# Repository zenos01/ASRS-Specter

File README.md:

# Fiber Optic FPV System

A **DIY Fiber Optic-enabled FPV video and control system** designed for affordable, high-performance drone operation. This system uses off-the-shelf components to deliver interference-free communication and advanced features at a cost of around **$300**.

## Key Features
- **Fiber Optic Communication**: Reliable and interference-free in challenging environments.
- **Customizable and Open Source**: Fully programmable, allowing for custom OSD elements, unique arming methods, and feature expansion.
- **High-Performance Video**:
  - Supports **1600x900 at 60fps** and **720p at 120fps**.
- **Advanced Capabilities**:
  - Real-time trajectory estimation for precise object dropping or landings.
  - Multi-camera support for enhanced situational awareness.
  - Ground station processing for greater computational power and flexibility.

## About the Project
This project aims to provide an affordable, flexible, and customizable alternative to traditional FPV systems. While still a prototype, it’s open to collaboration and feedback to refine and expand its capabilities.

## Getting Started
The **hardware guide** and **software guide** are currently a work in progress, but the basic setup will be updated soon. Stay tuned for detailed instructions!

## Contributing
Contributions are welcome! You can:
- Report issues via [GitHub Issues](link-to-issues).
- Suggest features or improvements.
- Submit pull requests to help refine the project.

---

Thank you.

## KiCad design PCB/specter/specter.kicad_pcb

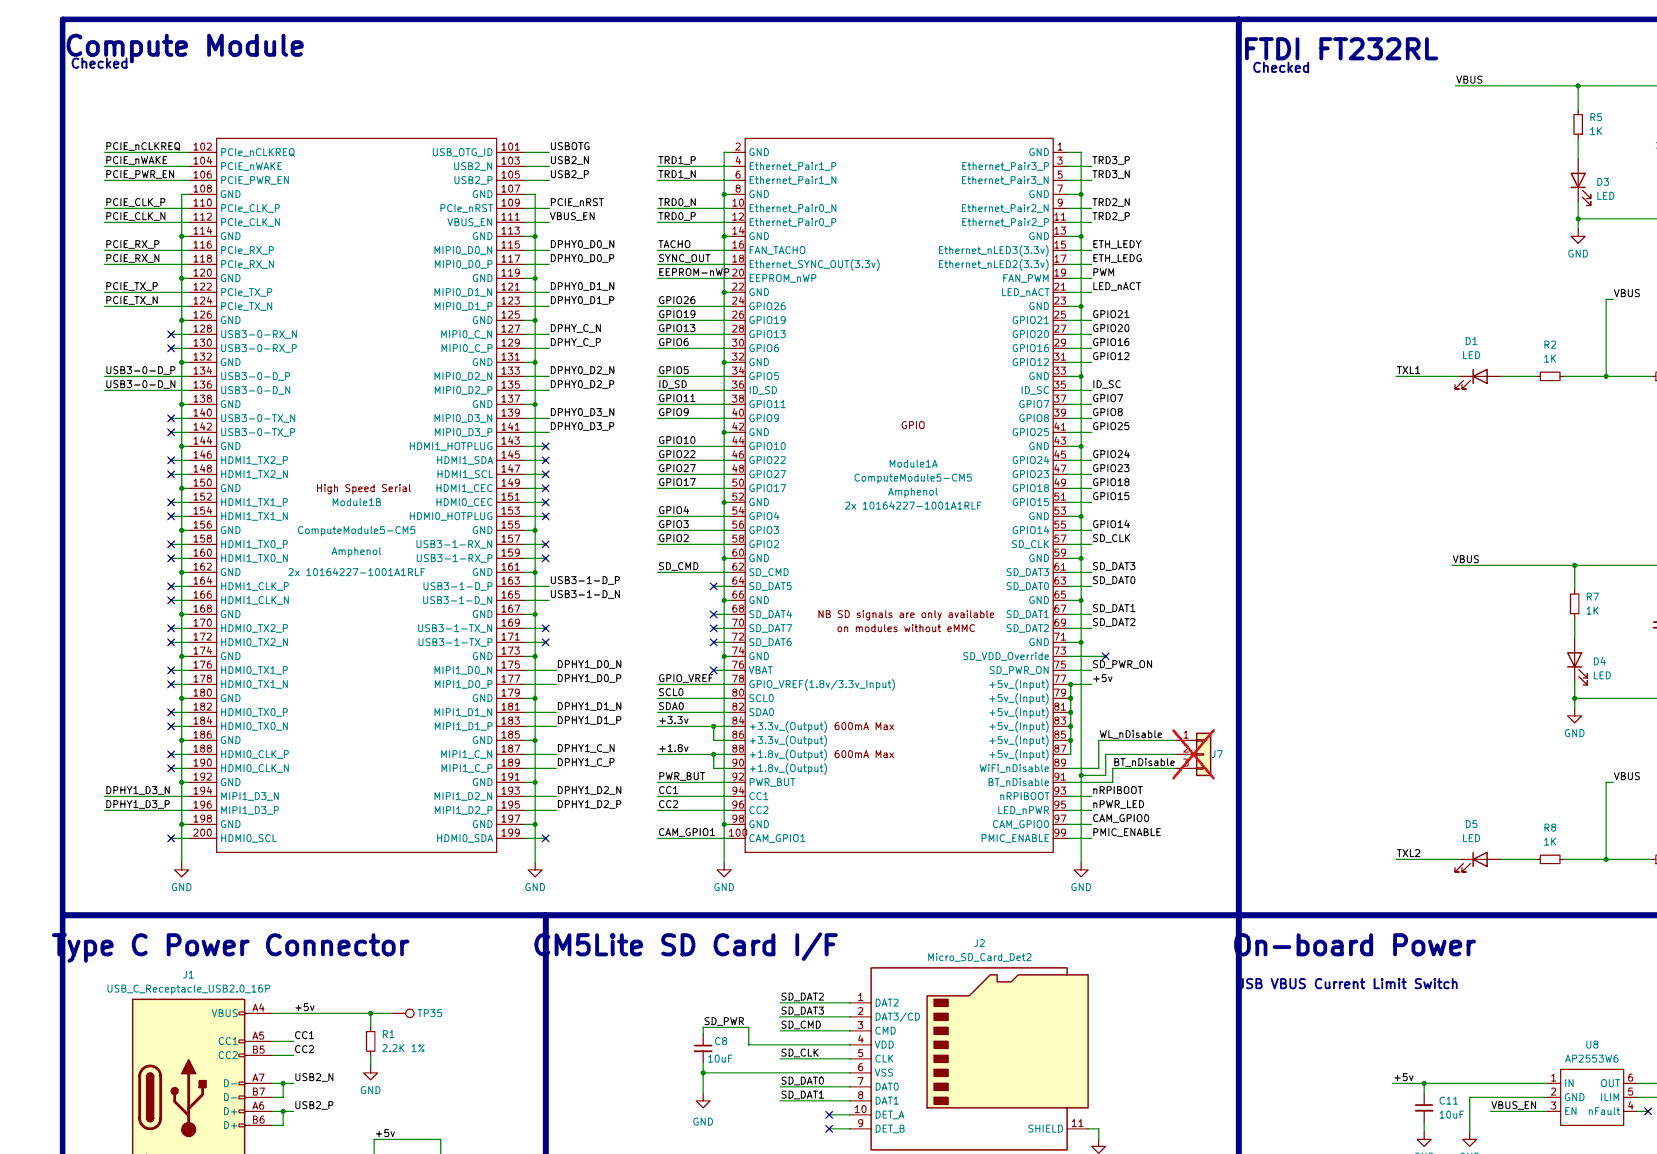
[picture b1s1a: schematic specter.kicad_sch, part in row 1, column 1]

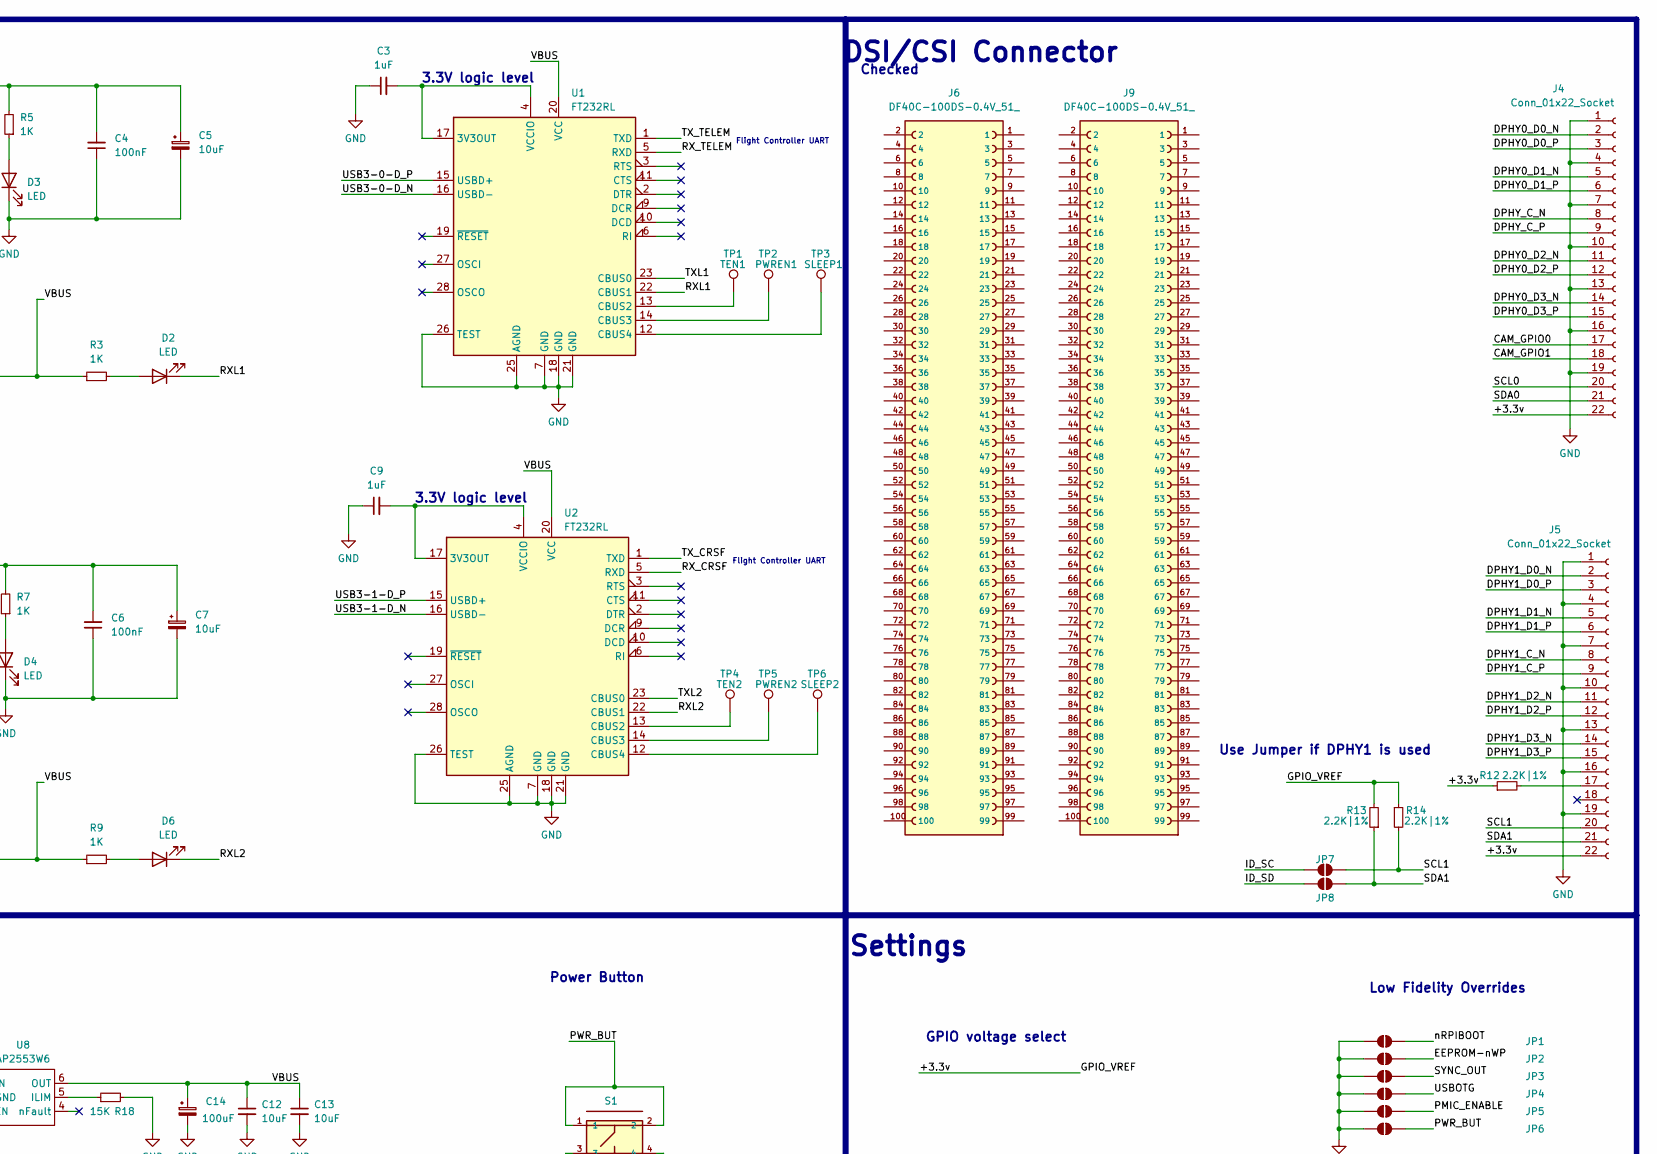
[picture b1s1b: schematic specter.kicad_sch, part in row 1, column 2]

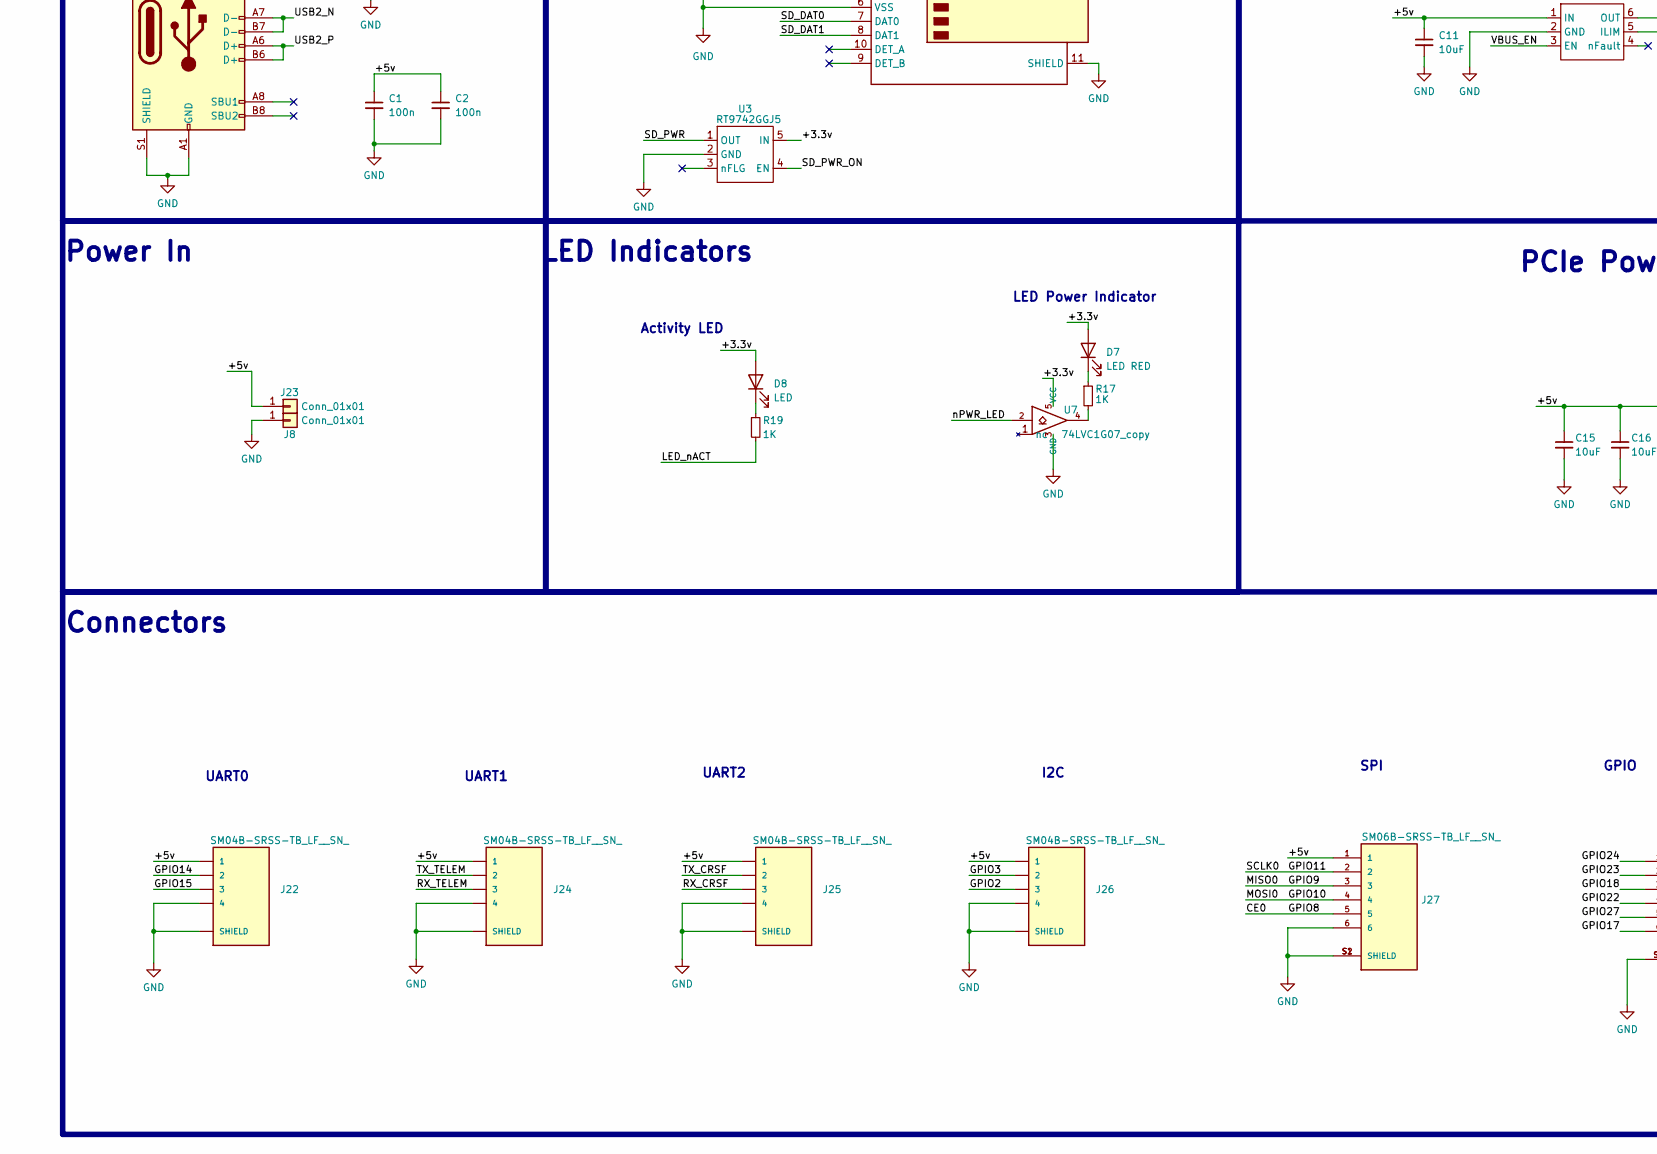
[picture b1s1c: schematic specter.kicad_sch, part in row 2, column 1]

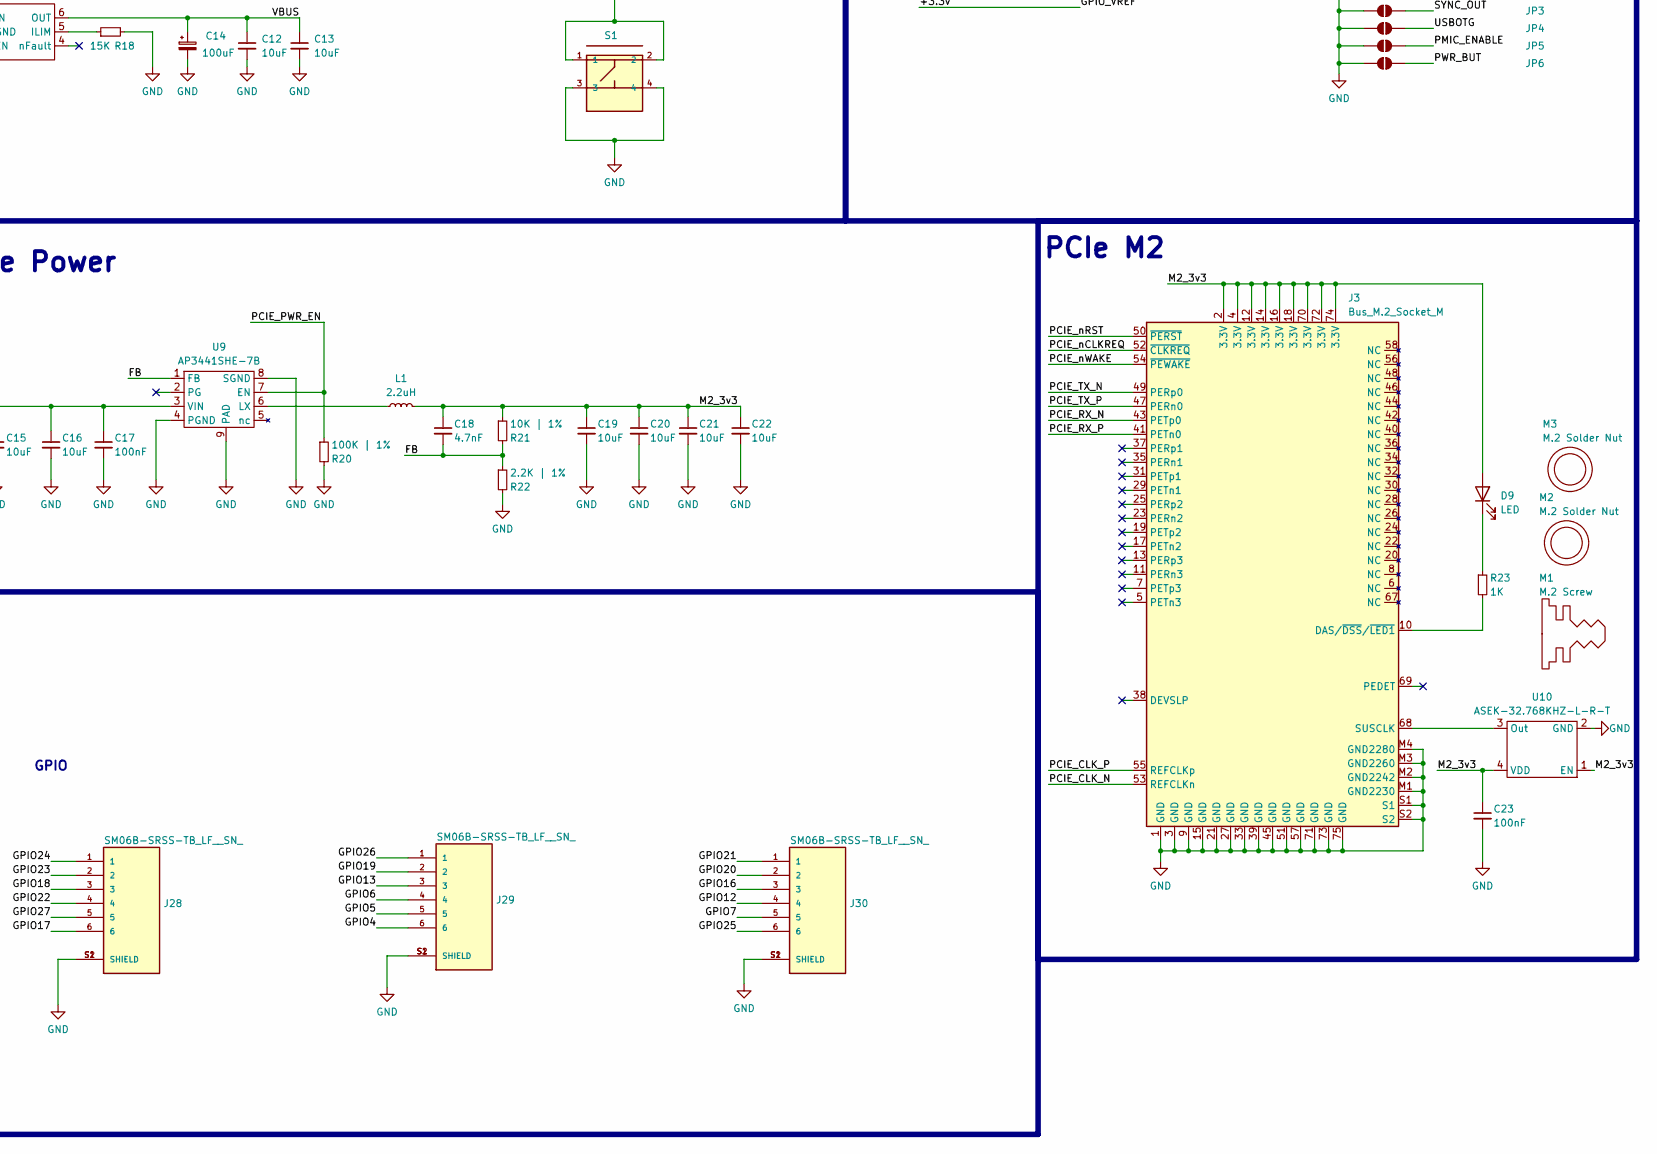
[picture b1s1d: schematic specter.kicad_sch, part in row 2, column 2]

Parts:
C1, C2: 100n; C_0402_1005Metric
C3, C9: 1uF; C_0805_2012Metric_Pad1.18x1.45mm_HandSolder
C4, C6: 100nF; C_0805_2012Metric_Pad1.18x1.45mm_HandSolder
C5, C7: 10uF; C_1206_3216Metric_Pad1.33x1.80mm_HandSolder
C8, C11, C12, C13, C15, C16, C19, C20, C21, C22: 10uF; C_0805_2012Metric
C14: 100uF; CP_EIA-7343-31_Kemet-D
C17, C23: 100nF; C_0402_1005Metric
C18: 4.7nF; C_0402_1005Metric
D1, D2, D3, D4, D5, D6, D9: LED; LED_0805_2012Metric_Pad1.15x1.40mm_HandSolder
D7: LED RED; LED_0603_1608Metric
D8: LED; LED_0603_1608Metric
J1: USB_C_Receptacle_USB2.0_16P; USB_C_Receptacle_GCT_USB4105-xx-A_16P_TopMnt_Horizontal
J2: Micro_SD_Card_Det2; SDCARD_MOLEX_503398-1892
J3: Bus_M.2_Socket_M; M.2 M Key socket
J4, J5: Conn_01x22_Socket; Hirose_FH12-22S-0.5SH_1x22-1MP_P0.50mm_Horizontal
J6, J9: DF40C-100DS-0.4V_51_; HIROSE_DF40C-100DS-0.4V_51_; PARTREV Oct.1.2023
J7: Conn_01x03; SolderJumper-3_P1.3mm_Open_RoundedPad1.0x1.5mm_NumberLabels; not fitted
J8, J23: Conn_01x01; TestPoint_THTPad_4.0x4.0mm_Drill2.0mm
J22, J24, J25, J26: SM04B-SRSS-TB_LF__SN_; JST_SM04B-SRSS-TB_LF__SN_
J27, J28, J29, J30: SM06B-SRSS-TB_LF__SN_; JST_SM06B-SRSS-TB_LF__SN_
JP1, JP2, JP3, JP4, JP5, JP6: SolderJumper_2_Open; SolderJumper-2_P1.3mm_Open_Pad1.0x1.5mm
JP7, JP8: SolderJumper_2_Open; SolderJumper-2_P1.3mm_Open_RoundedPad1.0x1.5mm
L1: 2.2uH; L_Bourns_SRP5030CC
M1: M.2 Screw
M2, M3: M.2 Solder Nut
Module1: ComputeModule5-CM5; Raspberry-Pi-5-Compute-Module
R1: 2.2K 1%; R_0402_1005Metric
R2, R3, R5, R7, R8, R9: 1K; R_0805_2012Metric_Pad1.20x1.40mm_HandSolder
R12, R13, R14: 2.2K|1%; R_0402_1005Metric
R17, R19, R23: 1K; R_0402_1005Metric
R18: 15K; R_0402_1005Metric
R20: 100K | 1%; R_0402_1005Metric
R21: 10K | 1%; R_0402_1005Metric
R22: 2.2K | 1%; R_0402_1005Metric
S1: SKQGAFE010; SW_SKQGAFE010; PART_REV B1
TP1: TEN1; TestPoint_Pad_D1.0mm
TP2: PWREN1; TestPoint_Pad_D1.0mm
TP3: SLEEP1; TestPoint_Pad_D1.0mm
TP4: TEN2; TestPoint_Pad_D1.0mm
TP5: PWREN2; TestPoint_Pad_D1.0mm
TP6: SLEEP2; TestPoint_Pad_D1.0mm
TP35: TestPoint; TestPoint_Pad_D1.0mm
U1, U2: FT232RL; SSOP-28_5.3x10.2mm_P0.65mm
U3: RT9742GGJ5; SOT-23-5
U7: 74LVC1G07_copy; SOT-353_SC-70-5
U8: AP2553W6; SOT-23-6
U9: AP3441SHE-7B; DFN-8-1EP_2x2mm_P0.5mm_EP1.05x1.75mm
U10: ASEK-32.768KHZ-L-R-T; Crystal_SMD_3225-4Pin_3.2x2.5mm

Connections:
/+1.8v: Module1.88 (+1.8v_(Output)), Module1.90 (+1.8v_(Output))
/+3.3v: D7.2 (A), D8.2 (A), J4.22, J5.22, Module1.78 (GPIO_VREF(1.8v/3.3v_Input)), Module1.84 (+3.3v_(Output)), Module1.86 (+3.3v_(Output)), R12.1, R13.2, R14.1, U3.5 (IN), U7.5 (VCC); also elsewhere on the board
/+5v: C1.1, C2.1, C11.1, C15.1, C16.1, C17.1, J1.A4 (VBUS), J1.A9 (VBUS), J1.B4 (VBUS), J1.B9 (VBUS), J22.1, J23.1, J24.1, J25.1, J26.1, J27.1, Module1.77 (+5v_(Input)), Module1.79 (+5v_(Input)), Module1.81 (+5v_(Input)), Module1.83 (+5v_(Input)), Module1.85 (+5v_(Input)), Module1.87 (+5v_(Input)), R1.1, TP35.1, U8.1 (IN), U9.3 (VIN)
/BT_nDisable: J7.3, Module1.91 (BT_nDisable)
/CAM_GPIO0: J4.17, Module1.97 (CAM_GPIO0)
/CAM_GPIO1: J4.18, Module1.100 (CAM_GPIO1)
/CC1: J1.A5 (CC1), Module1.94 (CC1)
/CC2: J1.B5 (CC2), Module1.96 (CC2)
/CE0: J27.5, Module1.39 (GPIO8)
/DPHY0_D0_N: J4.2, Module1.115 (MIPI0_D0_N)
/DPHY0_D0_P: J4.3, Module1.117 (MIPI0_D0_P)
/DPHY0_D1_N: J4.5, Module1.121 (MIPI0_D1_N)
/DPHY0_D1_P: J4.6, Module1.123 (MIPI0_D1_P)
/DPHY0_D2_N: J4.11, Module1.133 (MIPI0_D2_N)
/DPHY0_D2_P: J4.12, Module1.135 (MIPI0_D2_P)
/DPHY0_D3_N: J4.14, Module1.139 (MIPI0_D3_N)
/DPHY0_D3_P: J4.15, Module1.141 (MIPI0_D3_P)
/DPHY1_C_N: J5.8, Module1.187 (MIPI1_C_N)
/DPHY1_C_P: J5.9, Module1.189 (MIPI1_C_P)
/DPHY1_D0_N: J5.2, Module1.175 (MIPI1_D0_N)
/DPHY1_D0_P: J5.3, Module1.177 (MIPI1_D0_P)
/DPHY1_D1_N: J5.5, Module1.181 (MIPI1_D1_N)
/DPHY1_D1_P: J5.6, Module1.183 (MIPI1_D1_P)
/DPHY1_D2_N: J5.11, Module1.193 (MIPI1_D2_N)
/DPHY1_D2_P: J5.12, Module1.195 (MIPI1_D2_P)
/DPHY1_D3_N: J5.14, Module1.194 (MIPI1_D3_N)
/DPHY1_D3_P: J5.15, Module1.196 (MIPI1_D3_P)
/DPHY_C_N: J4.8, Module1.127 (MIPI0_C_N)
/DPHY_C_P: J4.9, Module1.129 (MIPI0_C_P)
/EEPROM-nWP: JP2.2 (B), Module1.20 (EEPROM_nWP)
/ETH_LEDG: Module1.17 (Ethernet_nLED2(3.3v))
/ETH_LEDY: Module1.15 (Ethernet_nLED3(3.3v))
/FB: C18.2, R21.2, R22.1, U9.1 (FB)
/GPIO2: J26.3, Module1.58 (GPIO2)
/GPIO3: J26.2, Module1.56 (GPIO3)
/GPIO4: J29.6, Module1.54 (GPIO4)
/GPIO5: J29.5, Module1.34 (GPIO5)
/GPIO6: J29.4, Module1.30 (GPIO6)
/GPIO7: J30.5, Module1.37 (GPIO7)
/GPIO9: J27.3, Module1.40 (GPIO9)
/GPIO10: J27.4, Module1.44 (GPIO10)
/GPIO11: J27.2, Module1.38 (GPIO11)
/GPIO12: J30.4, Module1.31 (GPIO12)
/GPIO13: J29.3, Module1.28 (GPIO13)
/GPIO14: J22.2, Module1.55 (GPIO14)
/GPIO15: J22.3, Module1.51 (GPIO15)
/GPIO16: J30.3, Module1.29 (GPIO16)
/GPIO17: J28.6, Module1.50 (GPIO17)
/GPIO18: J28.3, Module1.49 (GPIO18)
/GPIO19: J29.2, Module1.26 (GPIO19)
/GPIO20: J30.2, Module1.27 (GPIO20)
/GPIO21: J30.1, Module1.25 (GPIO21)
/GPIO22: J28.4, Module1.46 (GPIO22)
/GPIO23: J28.2, Module1.47 (GPIO23)
/GPIO24: J28.1, Module1.45 (GPIO24)
/GPIO25: J30.6, Module1.41 (GPIO25)
/GPIO26: J29.1, Module1.24 (GPIO26)
/GPIO27: J28.5, Module1.48 (GPIO27)
/ID_SC: JP7.1 (A), Module1.35 (ID_SC)
/ID_SD: JP8.1 (A), Module1.36 (ID_SD)
/LED_nACT: Module1.21 (LED_nACT), R19.2
/M2_3v3: C18.1, C19.1, C20.1, C21.1, C22.1, C23.1, D9.2 (A), J3.2 (3.3V), J3.4 (3.3V), J3.12 (3.3V), J3.14 (3.3V), J3.16 (3.3V), J3.18 (3.3V), J3.70 (3.3V), J3.72 (3.3V), J3.74 (3.3V), L1.2, R21.1, U10.1 (EN), U10.4 (VDD)
/PCIE_CLK_N: J3.53 (REFCLKn), Module1.112 (PCIe_CLK_N)
/PCIE_CLK_P: J3.55 (REFCLKp), Module1.110 (PCIe_CLK_P)
/PCIE_PWR_EN: Module1.106 (PCIE_PWR_EN), R20.1, U9.7 (EN)
/PCIE_RX_N: J3.43 (PETp0), Module1.118 (PCIe_RX_N)
/PCIE_RX_P: J3.41 (PETn0), Module1.116 (PCIe_RX_P)
/PCIE_TX_N: J3.49 (PERp0), Module1.124 (PCIe_TX_N)
/PCIE_TX_P: J3.47 (PERn0), Module1.122 (PCIe_TX_P)
/PCIE_nCLKREQ: J3.52 (~CLKREQ), Module1.102 (PCIe_nCLKREQ)
/PCIE_nRST: J3.50 (~PERST), Module1.109 (PCIe_nRST)
/PCIE_nWAKE: J3.54 (~PEWAKE), Module1.104 (PCIE_nWAKE)
/PMIC_ENABLE: JP5.2 (B), Module1.99 (PMIC_ENABLE)
/PWM: Module1.19 (FAN_PWM)
/PWR_BUT: JP6.2 (B), Module1.92 (PWR_BUT), S1.1, S1.2
/RXL1: D2.1 (K), U1.22 (CBUS1)
/RXL2: D6.1 (K), U2.22 (CBUS1)
/RX_CRSF: J25.3, U2.5 (RXD)
/RX_TELEM: J24.3, U1.5 (RXD)
/SCL0: J4.20, Module1.80 (SCL0)
/SCL1: J5.20, JP7.2 (B), R14.2
/SDA0: J4.21, Module1.82 (SDA0)
/SDA1: J5.21, JP8.2 (B), R13.1
/SD_CLK: J2.5 (CLK), Module1.57 (SD_CLK)
/SD_CMD: J2.3 (CMD), Module1.62 (SD_CMD)
/SD_DAT0: J2.7 (DAT0), Module1.63 (SD_DAT0)
/SD_DAT1: J2.8 (DAT1), Module1.67 (SD_DAT1)
/SD_DAT2: J2.1 (DAT2), Module1.69 (SD_DAT2)
/SD_DAT3: J2.2 (DAT3/CD), Module1.61 (SD_DAT3)
/SD_PWR: C8.1, J2.4 (VDD), U3.1 (OUT)
/SD_PWR_ON: Module1.75 (SD_PWR_ON), U3.4 (EN)
/SYNC_OUT: JP3.2 (B), Module1.18 (Ethernet_SYNC_OUT(3.3v))
/TACHO: Module1.16 (FAN_TACHO)
/TRD0_N: Module1.10 (Ethernet_Pair0_N)
/TRD0_P: Module1.12 (Ethernet_Pair0_P)
/TRD1_N: Module1.6 (Ethernet_Pair1_N)
/TRD1_P: Module1.4 (Ethernet_Pair1_P)
/TRD2_N: Module1.9 (Ethernet_Pair2_N)
/TRD2_P: Module1.11 (Ethernet_Pair2_P)
/TRD3_N: Module1.5 (Ethernet_Pair3_N)
/TRD3_P: Module1.3 (Ethernet_Pair3_P)
/TXL1: D1.1 (K), U1.23 (CBUS0)
/TXL2: D5.1 (K), U2.23 (CBUS0)
/TX_CRSF: J25.2, U2.1 (TXD)
/TX_TELEM: J24.2, U1.1 (TXD)
/USB2_N: J1.A7 (D-), J1.B7 (D-), Module1.103 (USB2_N)
/USB2_P: J1.A6 (D+), J1.B6 (D+), Module1.105 (USB2_P)
/USB3-0-D_N: Module1.136 (USB3-0-D_N), U1.16 (USBD-)
/USB3-0-D_P: Module1.134 (USB3-0-D_P), U1.15 (USBD+)
/USB3-1-D_N: Module1.165 (USB3-1-D_N), U2.16 (USBD-)
/USB3-1-D_P: Module1.163 (USB3-1-D_P), U2.15 (USBD+)
/USBOTG: JP4.2 (B), Module1.101 (USB_OTG_ID)
/VBUS: C4.2, C5.1, C6.2, C7.1, C12.1, C13.1, C14.1, R2.2, R3.1, R5.2, R7.2, R8.2, R9.1, U1.20 (VCC), U2.20 (VCC), U8.6 (OUT)
/VBUS_EN: Module1.111 (VBUS_EN), U8.3 (EN)
/WL_nDisable: J7.1, Module1.89 (WiFi_nDisable)
/nPWR_LED: Module1.95 (LED_nPWR), U7.2
/nRPIBOOT: JP1.2 (B), Module1.93 (nRPIBOOT)
GND: C1.2, C2.2, C3.1, C4.1, C5.2, C6.1, C7.2, C8.2, C9.1, C11.2, C12.2, C13.2, C14.2, C15.2, C16.2, C17.2, C19.2, C20.2, C21.2, C22.2, C23.2, D3.1 (K), D4.1 (K), J1.A1 (GND), J1.A12 (GND), J1.B1 (GND), J1.B12 (GND), J1.S1 (SHIELD), J2.6 (VSS), J2.11 (SHIELD), J3.1 (GND), J3.3 (GND), J3.9 (GND), J3.15 (GND), J3.21 (GND), J3.27 (GND), J3.33 (GND), J3.39 (GND), J3.45 (GND), J3.51 (GND), J3.57 (GND), J3.71 (GND), J3.73 (GND), J3.75 (GND), J3.M1 (GND2230), J3.M2 (GND2242), J3.M3 (GND2260), J3.M4 (GND2280), J3.S1, J3.S2, J4.1, J4.4, J4.7, J4.10, J4.13, J4.16, J4.19, J5.1, J5.4, J5.7, J5.10, J5.13, J5.16, J5.19, J7.2, J8.1, J22.4, J22.S1 (SHIELD), J22.S2 (SHIELD), J24.4, J24.S1 (SHIELD), J24.S2 (SHIELD), J25.4, J25.S1 (SHIELD), J25.S2 (SHIELD), J26.4, J26.S1 (SHIELD), J26.S2 (SHIELD), J27.6, J27.S1 (SHIELD), J27.S2 (SHIELD), J28.S1 (SHIELD), J28.S2 (SHIELD), J29.S1 (SHIELD), J29.S2 (SHIELD), J30.S1 (SHIELD), J30.S2 (SHIELD), JP1.1 (A), JP2.1 (A), JP3.1 (A), JP4.1 (A), JP5.1 (A), JP6.1 (A), Module1.1 (GND), Module1.2 (GND), Module1.7 (GND), Module1.8 (GND), Module1.13 (GND), Module1.14 (GND), Module1.22 (GND), Module1.23 (GND), Module1.32 (GND), Module1.33 (GND), Module1.42 (GND), Module1.43 (GND), Module1.52 (GND), Module1.53 (GND), Module1.59 (GND), Module1.60 (GND), Module1.65 (GND), Module1.66 (GND), Module1.71 (GND), Module1.74 (GND), Module1.98 (GND), Module1.107 (GND), Module1.108 (GND), Module1.113 (GND), Module1.114 (GND), Module1.119 (GND), Module1.120 (GND), Module1.125 (GND), Module1.126 (GND), Module1.131 (GND), Module1.132 (GND), Module1.137 (GND), Module1.138 (GND), Module1.144 (GND), Module1.150 (GND), Module1.155 (GND), Module1.156 (GND), Module1.161 (GND), Module1.162 (GND), Module1.167 (GND), Module1.168 (GND), Module1.173 (GND), Module1.174 (GND), Module1.179 (GND), Module1.180 (GND), Module1.185 (GND), Module1.186 (GND), Module1.191 (GND), Module1.192 (GND), Module1.197 (GND), Module1.198 (GND), R1.2, R18.2, R20.2, R22.2, S1.3, S1.4, U1.7 (GND), U1.18 (GND), U1.21 (GND), U1.25 (AGND), U1.26 (TEST), U2.7 (GND), U2.18 (GND), U2.21 (GND), U2.25 (AGND), U2.26 (TEST), U3.2 (GND), U7.3 (GND), U8.2 (GND), U9.4 (PGND), U9.8 (SGND), U9.9 (PAD), U10.2 (GND)
unnamed: D1.2 (A), R2.1
unnamed: D2.2 (A), R3.2
unnamed: D3.2 (A), R5.1
unnamed: D4.2 (A), R7.1
unnamed: D5.2 (A), R8.1
unnamed: D6.2 (A), R9.2
unnamed: D7.1 (K), R17.1
unnamed: D8.1 (K), R19.1
unnamed: D9.1 (K), R23.1
unnamed: J3.10 (DAS/~DSS/~LED1), R23.2
unnamed: J3.68 (SUSCLK), U10.3 (Out)
unnamed: J5.17, R12.2
unnamed: R17.2, U7.4
unnamed: C3.2, U1.4 (VCCIO), U1.17 (3V3OUT)
unnamed: TP1.1, U1.13 (CBUS2)
unnamed: TP2.1, U1.14 (CBUS3)
unnamed: TP3.1, U1.12 (CBUS4)
unnamed: C9.2, U2.4 (VCCIO), U2.17 (3V3OUT)
unnamed: TP4.1, U2.13 (CBUS2)
unnamed: TP5.1, U2.14 (CBUS3)
unnamed: TP6.1, U2.12 (CBUS4)
unnamed: R18.1, U8.5 (ILIM)
unnamed: L1.1, U9.6 (LX)

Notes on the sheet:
Checked
3.3V logic level
Low Fidelity Overrides
PCIe M2
PCIe Power
SPI
UART2
Activity LED
UART0
GPIO
LED Indicators
Type C Power Connector
I2C
Flight Controller UART
GPIO voltage select
UART1
Connectors
Settings
FTDI FT232RL
Use Jumper if DPHY1 is used
CM5Lite SD Card I/F
Power Button
LED Power Indicator
Compute Module
Power In
On-board Power
USB VBUS Current Limit Switch
DSI/CSI Connector

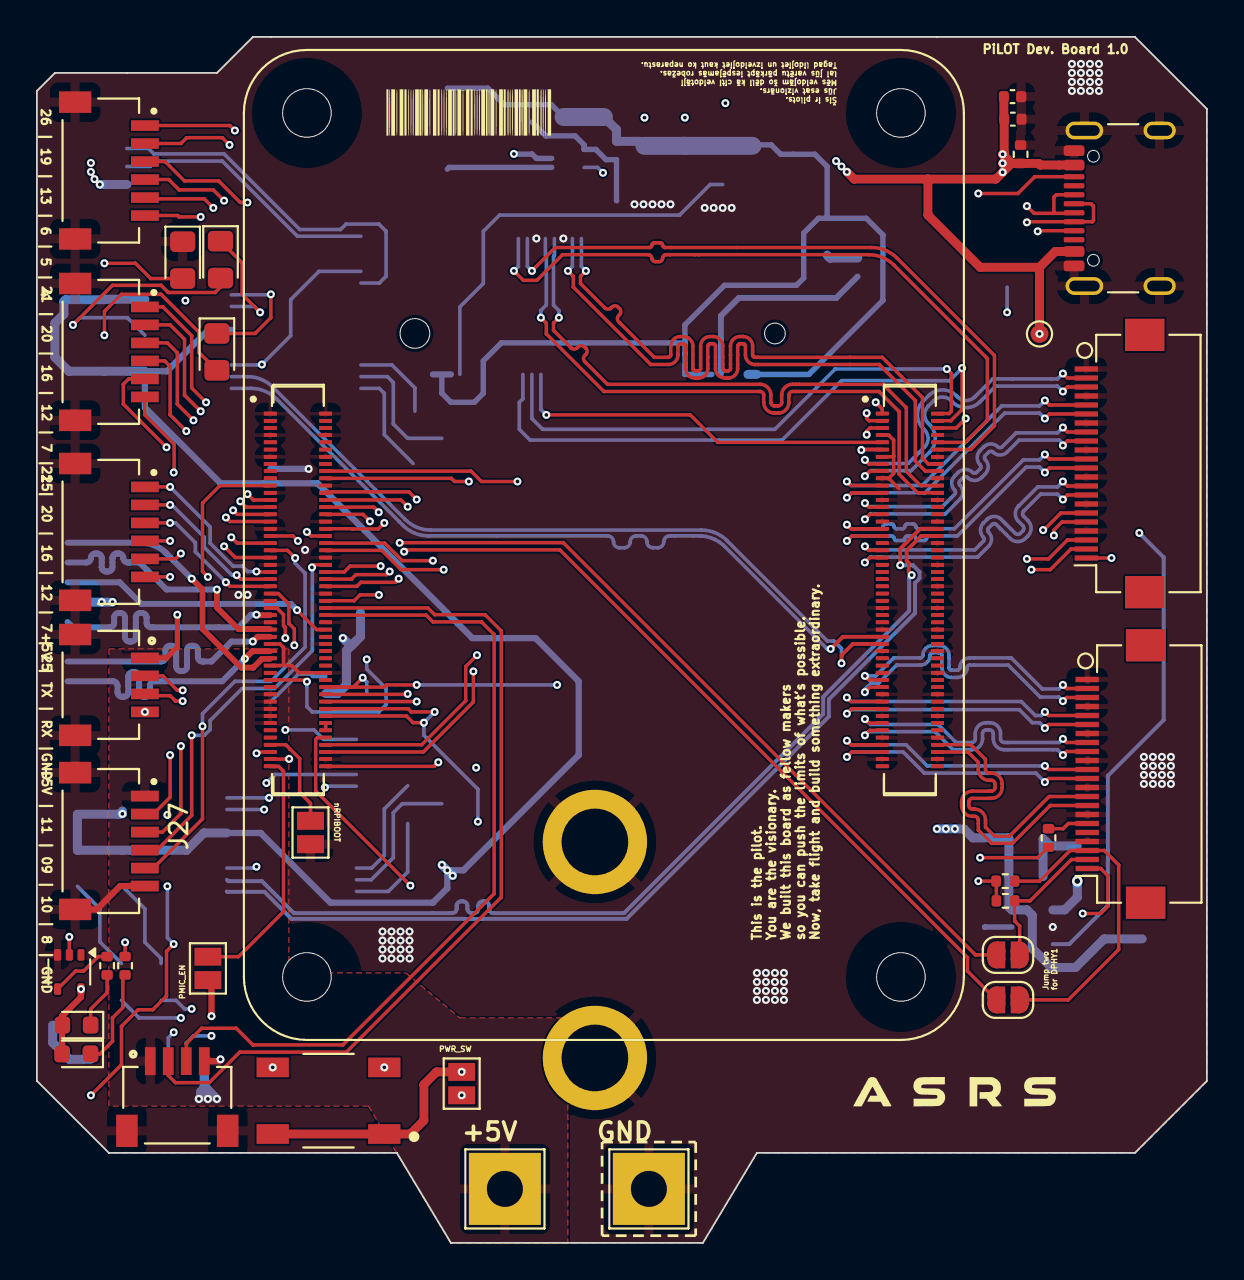
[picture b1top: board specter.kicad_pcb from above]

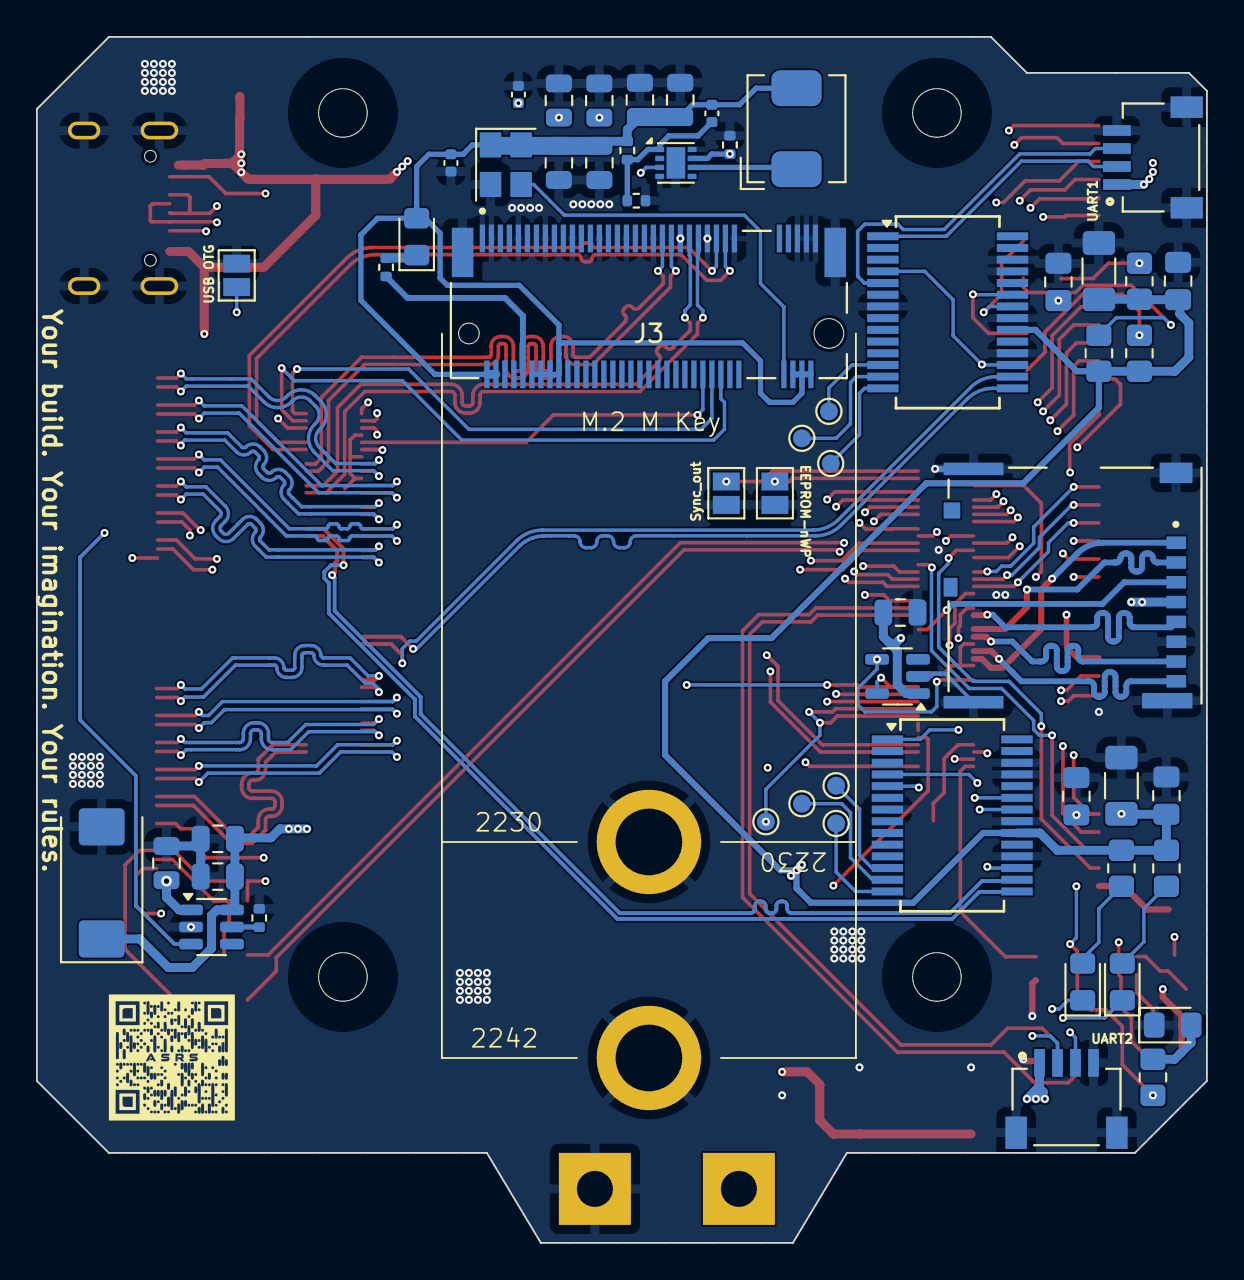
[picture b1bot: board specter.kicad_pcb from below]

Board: 4 copper layers, 65.0 x 67.0 mm, 91 parts (56 on the bottom side), 127 nets.

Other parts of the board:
TP33: TestPoint; TestPoint_Pad_D1.0mm

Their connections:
/+3.3v: TP33.1; also elsewhere on the board

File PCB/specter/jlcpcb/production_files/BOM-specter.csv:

Comment,Designator,Footprint,LCSC,Quantity
1K,"R17,R19,R23",R_0402_1005Metric,C11702,3
100uF,C14,CP_EIA-7343-31_Kemet-D,C122321,1
10uF,"C5,C7",C_1206_3216Metric_Pad1.33x1.80mm_HandSolder,C13585,2
Bus_M.2_Socket_M,J3,M.2 M Key socket,C1509730,1
100n,"C1,C17,C2,C23",C_0402_1005Metric,C1525,4
4.7nF,C18,C_0402_1005Metric,C1538,1
10uF,"C11,C12,C13,C15,C16,C19,C20,C21,C22,C8",C_0805_2012Metric,C15850,10
SM04B-SRSS-TB_LF__SN_,"J22,J24,J25,J26",JST_SM04B-SRSS-TB_LF__SN_,C160404,4
1K,"R2,R3,R5,R7,R8,R9",R_0805_2012Metric_Pad1.20x1.40mm_HandSolder,C17513,6
SKQGAFE010,S1,SW_SKQGAFE010,C202424,1
AP3441SHE-7B,U9,DFN-8-1EP_2x2mm_P0.5mm_EP1.05x1.75mm,C2070918,1
AP2553W6,U8,SOT-23-6,C212302,1
2.2uH,L1,L_Bourns_SRP5030CC,C22404330,1
LED RED,"D7,D8",LED_0603_1608Metric,C2290,2
LED,"D1,D2,D5,D6,D9",LED_0805_2012Metric_Pad1.15x1.40mm_HandSolder,C2297,5
RT9742GGJ5,U3,SOT-23-5,C250547,1
100K | 1%,R20,R_0402_1005Metric,C25741,1
10K | 1%,R21,R_0402_1005Metric,C25744,1
15K,R18,R_0402_1005Metric,C25756,1
2.2K 1%,"R1,R12,R13,R14,R22",R_0402_1005Metric,C25879,5
ASEK-32.768KHZ-L-R-T,U10,Crystal_SMD_3225-4Pin_3.2x2.5mm,C2650753,1
1uF,"C3,C9",C_0805_2012Metric_Pad1.18x1.45mm_HandSolder,C28323,2
LED,"D3,D4",LED_0805_2012Metric_Pad1.15x1.40mm_HandSolder,C34499,2
DF40C-100DS-0.4V_51_,"J6,J9",HIROSE_DF40C-100DS-0.4V_51_,C3642394,2
Micro_SD_Card_Det2,J2,SDCARD_MOLEX_503398-1892,C428492,1
100nF,"C4,C6",C_0805_2012Metric_Pad1.18x1.45mm_HandSolder,C49678,2
74LVC1G07_copy,U7,SOT-353_SC-70-5,C5138996,1
USB_C_Receptacle_USB2.0_16P,J1,USB_C_Receptacle_GCT_USB4105-xx-A_16P_TopMnt_Horizontal,C5187472,1
Conn_01x22_Socket,"J4,J5",Hirose_FH12-22S-0.5SH_1x22-1MP_P0.50mm_Horizontal,C597981,2
FT232RL,"U1,U2",SSOP-28_5.3x10.2mm_P0.65mm,C8690,2
SM06B-SRSS-TB_LF__SN_,"J27,J28,J29,J30",JST_SM06B-SRSS-TB_LF__SN_,C9900025724,4

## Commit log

2025-01-23 Create README.md
    Template
2025-01-23 Update README.md
    updated readme
2025-01-23 Update README.md
    small changes
2025-01-26 added schematic PCB
2025-02-03 pre-check schematic layout
2025-02-09 added PCIe to PCBA
2025-02-09 added PCIe slot
2025-02-11 started PCB layout
2025-02-13 updated PCB layout
2025-02-16 started PCB traces
2025-02-21 impedance matching
2025-03-02 updated to use gstreamer
2025-03-02 updated gstreamer usage
2025-03-06 final gstreamer implementation
2025-03-07 added gstreamer to aircraft side
2025-03-11 updated PCB
2025-03-14 added SD card routing
2025-03-17 GPIO wired
2025-03-18 finalised routing on PCB
2025-03-25 small PCB updates
2025-03-25 power lanes PCB
2025-03-25 added power planes
2025-03-26 finished PCB first round
2025-03-26 added last minute changes
2025-04-13 refined PCB
2025-04-13 finishing touches
2025-04-15 added 3D models
2025-05-07 final PCB changes
2025-05-20 added JLC options
